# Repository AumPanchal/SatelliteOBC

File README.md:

# Satellite Onboard Computer

This is a small computer for a satellite that I designed and programmed. It reads sensors, checks that everything is working, saves faults to flash memory, and sends data to a Python program on a PC.

Made with KiCad, STM32, C, Python, I2C, SPI, UART and CRC-16.

## What's on the board

- STM32F411 microcontroller
- Two MPU-9250 motion sensors (two so one can back up the other)
- TMP117 temperature sensor
- INA226 voltage and current monitor
- W25Q32 flash memory for saving faults
- AMS1117 3.3V regulator

The board is 2 layers and passes the KiCad ERC and DRC checks.

## How the firmware works

The firmware is written in C and has four states:

- **BOOT**: sets up the hardware
- **SELF_TEST**: checks that every sensor and the flash respond
- **NOMINAL**: normal operation, reads sensors and sends data 10 times a second
- **SAFE_MODE**: something went wrong, so the fault is saved to flash and the computer waits for the ground station

If a sensor fails, the two motion sensors disagree, or a value goes out of range, it switches to SAFE_MODE and saves an error code to flash. A hardware watchdog resets the chip if the firmware freezes.

## Talking to the computer

The board sends data over UART at 115200 baud. Each message has a CRC-16 so the PC can tell if it got corrupted. The ground station can also send commands (ping, safe mode, recover, read the fault log, clear the log, reboot) and gets back an ACK or NACK.

## Folders

- `firmware/src`: the C code
- `ground_station`: the Python program
- `hardware`: KiCad files

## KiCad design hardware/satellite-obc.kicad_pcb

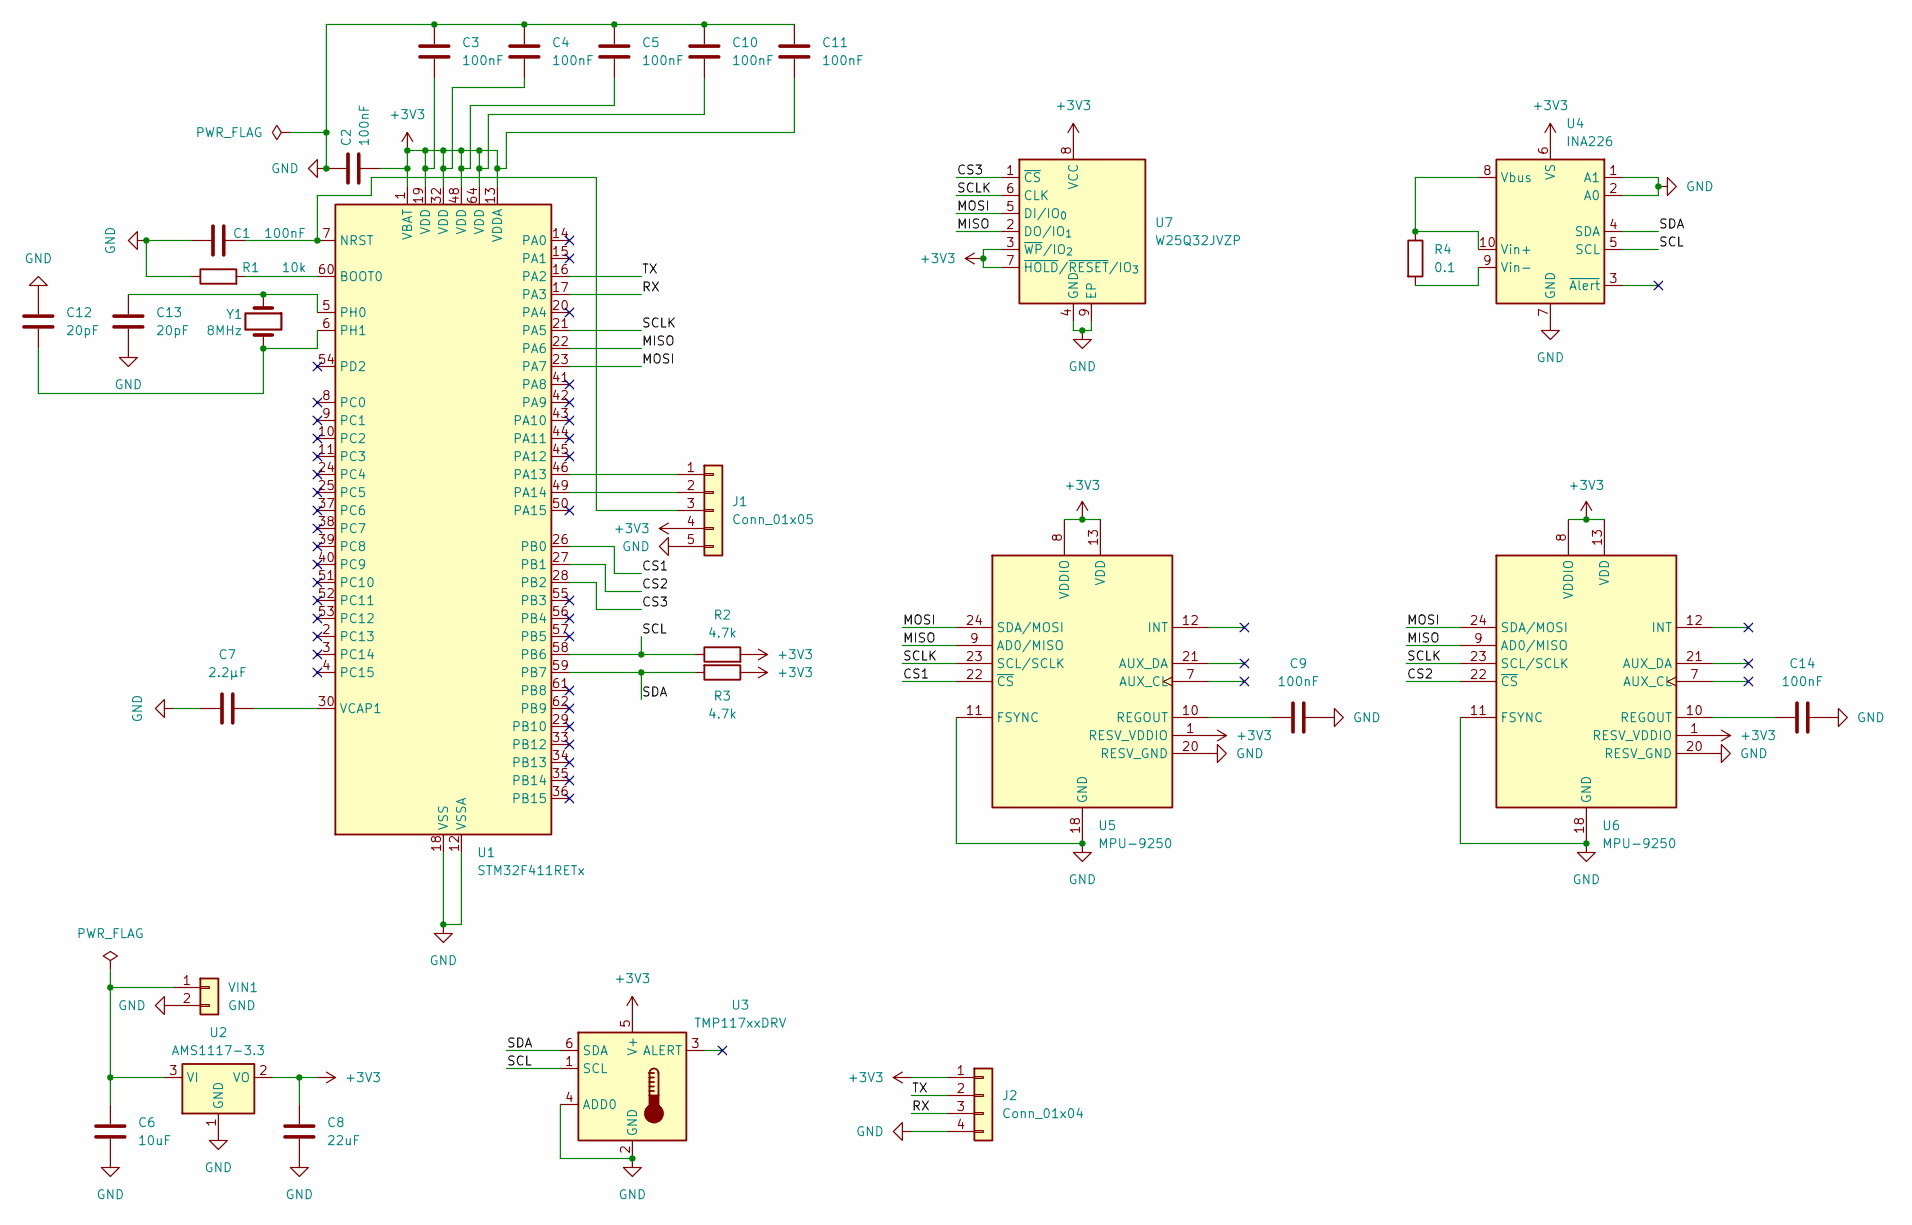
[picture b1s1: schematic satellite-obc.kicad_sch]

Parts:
C1, C2, C3, C4, C5, C9, C10, C11, C14: 100nF; C_0805_2012Metric
C6: 10uF; C_0805_2012Metric
C7: 2.2µF; C_0805_2012Metric
C8: 22uF; C_0805_2012Metric
C12, C13: 20pF; C_0805_2012Metric
J1: Conn_01x05; PinHeader_1x05_P2.54mm_Vertical
J2: Conn_01x04; PinHeader_1x04_P2.54mm_Vertical
R1: 10k; R_0805_2012Metric
R2, R3: 4.7k; R_0805_2012Metric
R4: 0.1; R_0805_2012Metric
U1: STM32F411RETx; LQFP-64_10x10mm_P0.5mm
U2: AMS1117-3.3; SOT-223-3_TabPin2
U3: TMP117xxDRV; WSON-6-1EP_2x2mm_P0.65mm_EP1x1.6mm
U4: INA226; TSSOP-10_3x3mm_P0.5mm
U5, U6: MPU-9250; InvenSense_QFN-24_3x3mm_P0.4mm
U7: W25Q32JVZP; WSON-8-1EP_6x5mm_P1.27mm_EP3.4x4.3mm
VIN1: GND; PinHeader_1x02_P2.54mm_Vertical
Y1: 8MHz; Crystal_HC49-4H_Vertical

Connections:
+3V3: C2.2, C3.2, C4.2, C5.2, C8.1, C10.2, C11.2, J1.4, J2.1, R2.2, R3.1, U1.1 (VBAT), U1.13 (VDDA), U1.19 (VDD), U1.32 (VDD), U1.48 (VDD), U1.64 (VDD), U2.2 (VO), U3.5 (V+), U4.6 (VS), U5.1 (RESV_VDDIO), U5.8 (VDDIO), U5.13 (VDD), U6.1 (RESV_VDDIO), U6.8 (VDDIO), U6.13 (VDD), U7.3 (~WP/IO_{2}), U7.7 (~HOLD/~RESET/IO_{3}), U7.8 (VCC)
/CS1: U1.26 (PB0), U5.22 (~CS)
/CS2: U1.27 (PB1), U6.22 (~CS)
/CS3: U1.28 (PB2), U7.1 (~CS)
/MISO: U1.22 (PA6), U5.9 (AD0/MISO), U6.9 (AD0/MISO), U7.2 (DO/IO_{1})
/MOSI: U1.23 (PA7), U5.24 (SDA/MOSI), U6.24 (SDA/MOSI), U7.5 (DI/IO_{0})
/RX: J2.3, U1.17 (PA3)
/SCL: R2.1, U1.58 (PB6), U3.1 (SCL), U4.5 (SCL)
/SCLK: U1.21 (PA5), U5.23 (SCL/SCLK), U6.23 (SCL/SCLK), U7.6 (CLK)
/SDA: R3.2, U1.59 (PB7), U3.6 (SDA), U4.4 (SDA)
/TX: J2.2, U1.16 (PA2)
GND: C1.1, C2.1, C3.1, C4.1, C5.1, C6.2, C7.1, C8.2, C9.2, C10.1, C11.1, C12.1, C13.2, C14.2, J1.5, J2.4, R1.1, U1.12 (VSSA), U1.18 (VSS), U1.31 (VSS), U1.47 (VSS), U1.63 (VSS), U2.1 (GND), U3.2 (GND), U3.4 (ADD0), U4.1 (A1), U4.2 (A0), U4.7 (GND), U5.11 (FSYNC), U5.18 (GND), U5.20 (RESV_GND), U6.11 (FSYNC), U6.18 (GND), U6.20 (RESV_GND), U7.4 (GND), U7.9 (EP), VIN1.2
unnamed: J1.1, U1.46 (PA13)
unnamed: J1.2, U1.49 (PA14)
unnamed: C1.2, J1.3, U1.7 (NRST)
unnamed: R1.2, U1.60 (BOOT0)
unnamed: C13.1, U1.5 (PH0), Y1.1
unnamed: C12.2, U1.6 (PH1), Y1.2
unnamed: C7.2, U1.30 (VCAP1)
unnamed: C6.1, U2.3 (VI), VIN1.1
unnamed: R4.1, U4.8 (Vbus), U4.10 (Vin+)
unnamed: R4.2, U4.9 (Vin-)
unnamed: C9.1, U5.10 (REGOUT)
unnamed: C14.1, U6.10 (REGOUT)

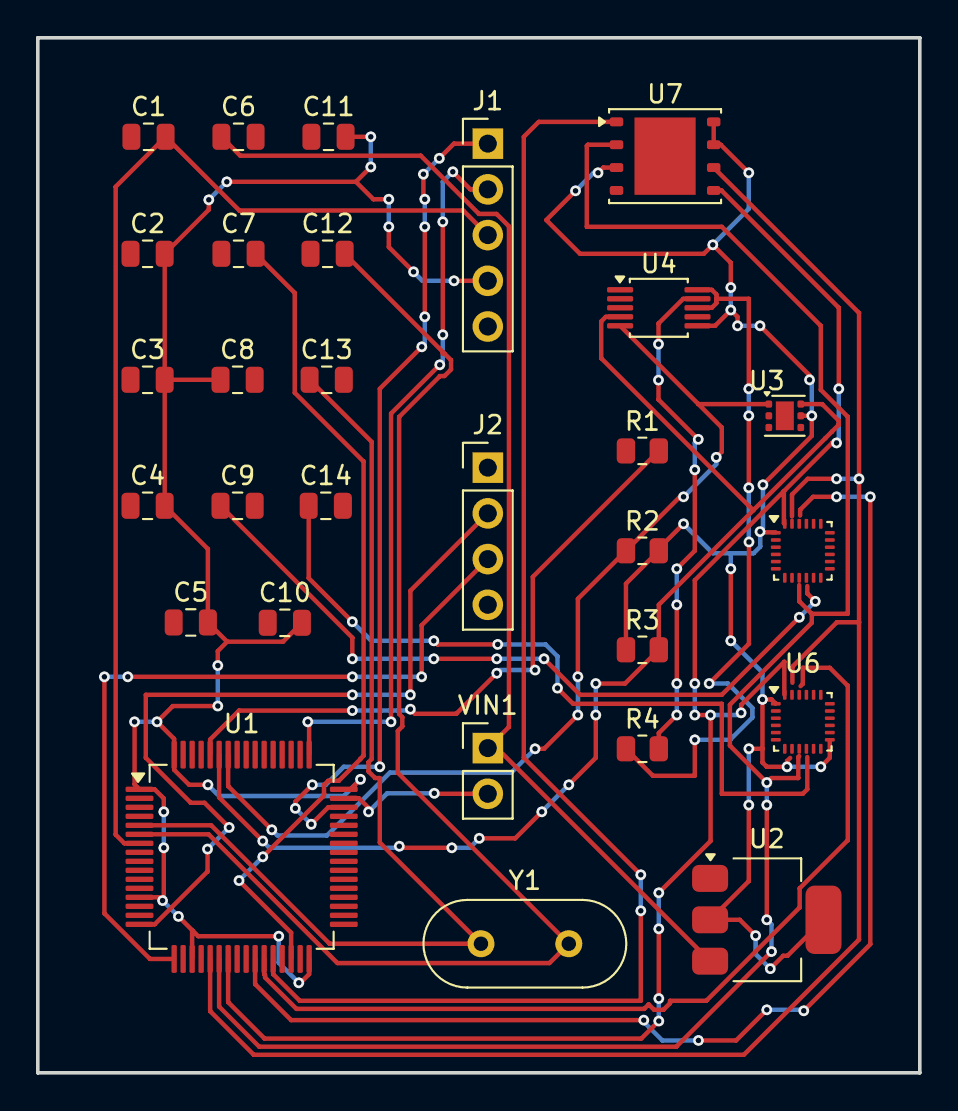
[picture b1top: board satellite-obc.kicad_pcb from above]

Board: 2 copper layers, 49.0 x 57.5 mm, 29 parts (0 on the bottom side), 24 nets.

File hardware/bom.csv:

"Reference","Qty","Value","DNP","Exclude from BOM","Exclude from Board","Footprint","Datasheet"
"C1,C2,C3,C4,C5,C9,C10,C11,C14","9","100nF","","","","Capacitor_SMD:C_0805_2012Metric",""
"C6","1","10uF","","","","Capacitor_SMD:C_0805_2012Metric",""
"C7","1","2.2µF","","","","Capacitor_SMD:C_0805_2012Metric",""
"C8","1","22uF","","","","Capacitor_SMD:C_0805_2012Metric",""
"C12,C13","2","20pF","","","","Capacitor_SMD:C_0805_2012Metric",""
"J1","1","Conn_01x05","","","","Connector_PinHeader_2.54mm:PinHeader_1x05_P2.54mm_Vertical",""
"J2","1","Conn_01x04","","","","Connector_PinHeader_2.54mm:PinHeader_1x04_P2.54mm_Vertical",""
"R1","1","10k","","","","Resistor_SMD:R_0805_2012Metric",""
"R2,R3","2","4.7k","","","","Resistor_SMD:R_0805_2012Metric",""
"R4","1","0.1","","","","Resistor_SMD:R_0805_2012Metric",""
"U1","1","STM32F411RETx","","","","Package_QFP:LQFP-64_10x10mm_P0.5mm","https://www.st.com/resource/en/datasheet/stm32f411re.pdf"
"U2","1","AMS1117-3.3","","","","Package_TO_SOT_SMD:SOT-223-3_TabPin2","http://www.advanced-monolithic.com/pdf/ds1117.pdf"
"U3","1","TMP117xxDRV","","","","Package_SON:WSON-6-1EP_2x2mm_P0.65mm_EP1x1.6mm","https://www.ti.com/lit/ds/symlink/tmp117.pdf"
"U4","1","INA226","","","","Package_SO:TSSOP-10_3x3mm_P0.5mm","http://www.ti.com/lit/ds/symlink/ina226.pdf"
"U5,U6","2","MPU-9250","","","","Sensor_Motion:InvenSense_QFN-24_3x3mm_P0.4mm","https://invensense.tdk.com/wp-content/uploads/2015/02/PS-MPU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"
"U7","1","W25Q32JVZP","","","","Package_SON:WSON-8-1EP_6x5mm_P1.27mm_EP3.4x4.3mm","http://www.winbond.com/resource-files/w25q32jv%20revg%200327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"
"VIN1","1","GND","","","","Connector_PinHeader_2.54mm:PinHeader_1x02_P2.54mm_Vertical",""
"Y1","1","8MHz","","","","Crystal:Crystal_HC49-4H_Vertical",""

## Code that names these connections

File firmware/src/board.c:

#include "stm32f4xx.h"
#include "board.h"
#include "config.h"

uint32_t g_sysclk_hz = 16000000;
uint32_t g_pclk1_hz  = 16000000;
uint32_t g_pclk2_hz  = 16000000;

static volatile uint32_t ms_ticks;

int clock_init(void)
{
    uint32_t t;

    // start the 8 MHz crystal
    RCC->CR |= RCC_CR_HSEON;
    for (t = 0; t < 500000 && !(RCC->CR & RCC_CR_HSERDY); t++) {}
    if (!(RCC->CR & RCC_CR_HSERDY)) {
        RCC->CR &= ~RCC_CR_HSEON;
        return -1;                   // stay on internal 16 MHz
    }

    RCC->APB1ENR |= RCC_APB1ENR_PWREN;
    FLASH->ACR = FLASH_ACR_ICEN | FLASH_ACR_DCEN | FLASH_ACR_PRFTEN | FLASH_ACR_LATENCY_2WS;

    // 8 MHz /4 *168 /4 = 84 MHz
    RCC->PLLCFGR = (4u << RCC_PLLCFGR_PLLM_Pos) |
                   (168u << RCC_PLLCFGR_PLLN_Pos) |
                   (1u << RCC_PLLCFGR_PLLP_Pos) |
                   RCC_PLLCFGR_PLLSRC_HSE |
                   (7u << RCC_PLLCFGR_PLLQ_Pos);

    RCC->CR |= RCC_CR_PLLON;
    for (t = 0; t < 500000 && !(RCC->CR & RCC_CR_PLLRDY); t++) {}
    if (!(RCC->CR & RCC_CR_PLLRDY)) {
        RCC->CR &= ~(RCC_CR_PLLON | RCC_CR_HSEON);
        return -1;
    }

    // APB1 = 42 MHz, APB2 = 84 MHz
    RCC->CFGR = RCC_CFGR_HPRE_DIV1 | RCC_CFGR_PPRE1_DIV2 | RCC_CFGR_PPRE2_DIV1 | RCC_CFGR_SW_PLL;
    for (t = 0; t < 500000 && (RCC->CFGR & RCC_CFGR_SWS) != RCC_CFGR_SWS_PLL; t++) {}

    g_sysclk_hz = 84000000;
    g_pclk1_hz  = 42000000;
    g_pclk2_hz  = 84000000;
    return 0;
}

void systick_init(void)
{
    SysTick_Config(g_sysclk_hz / 1000);   // 1 ms tick
}

void SysTick_Handler(void)
{
    ms_ticks++;
}

uint32_t millis(void)
{
    return ms_ticks;
}

void delay_ms(uint32_t ms)
{
    uint32_t start = ms_ticks;
    while (ms_ticks - start < ms) {
        wdg_kick();
    }
}

static void pin_mode(GPIO_TypeDef *g, uint8_t pin, uint8_t mode)
{
    g->MODER = (g->MODER & ~(3u << (pin * 2)))  | ((uint32_t)mode << (pin * 2));
}

static void pin_af(GPIO_TypeDef *g, uint8_t pin, uint8_t af)
{
    uint8_t reg = pin >> 3;
    uint8_t pos = (pin & 7) * 4;
    g->AFR[reg] = (g->AFR[reg] & ~(0xFu << pos)) | ((uint32_t)af << pos);
    pin_mode(g, pin, 2);
    g->OSPEEDR |= 3u << (pin * 2);
}

void gpio_init(void)
{
    RCC->AHB1ENR |= RCC_AHB1ENR_GPIOAEN | RCC_AHB1ENR_GPIOBEN;

    // PA2 / PA3 -> USART2 TX / RX
    pin_af(GPIOA, 2, 7);
    pin_af(GPIOA, 3, 7);

    // PA5 / PA6 / PA7 -> SPI1 SCK / MISO / MOSI
    pin_af(GPIOA, 5, 5);
    pin_af(GPIOA, 6, 5);
    pin_af(GPIOA, 7, 5);

    // PB6 / PB7 -> I2C1 SCL / SDA (open drain, external 4.7k pullups)
    pin_af(GPIOB, 6, 4);
    pin_af(GPIOB, 7, 4);
    GPIOB->OTYPER |= (1u << 6) | (1u << 7);

    // PB0 / PB1 / PB2 -> chip selects, idle high
    GPIOB->BSRR = (1u << 0) | (1u << 1) | (1u << 2);
    pin_mode(GPIOB, 0, 1);
    pin_mode(GPIOB, 1, 1);
    pin_mode(GPIOB, 2, 1);
    GPIOB->OSPEEDR |= (3u << 0) | (3u << 2) | (3u << 4);
}

void wdg_init(void)
{
    DBGMCU->APB1FZ |= DBGMCU_APB1_FZ_DBG_IWDG_STOP;   // pause watchdog when debugging
    IWDG->KR = 0xCCCC;                                // start
    IWDG->KR = 0x5555;                                // unlock config
    IWDG->PR = 3;                                     // LSI / 32
    IWDG->RLR = WDG_TIMEOUT_MS;                       // ~1 kHz clock -> ~1 s
    while (IWDG->SR) {}
    IWDG->KR = 0xAAAA;
}

void wdg_kick(void)
{
    IWDG->KR = 0xAAAA;
}

uint8_t reset_by_watchdog(void)
{
    uint8_t r = (RCC->CSR & RCC_CSR_IWDGRSTF) ? 1 : 0;
    RCC->CSR |= RCC_CSR_RMVF;    // clear reset flags
    return r;
}

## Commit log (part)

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2026-06-02 phase 0 commit
2026-06-02 Add initial README for Satellite OBC project
